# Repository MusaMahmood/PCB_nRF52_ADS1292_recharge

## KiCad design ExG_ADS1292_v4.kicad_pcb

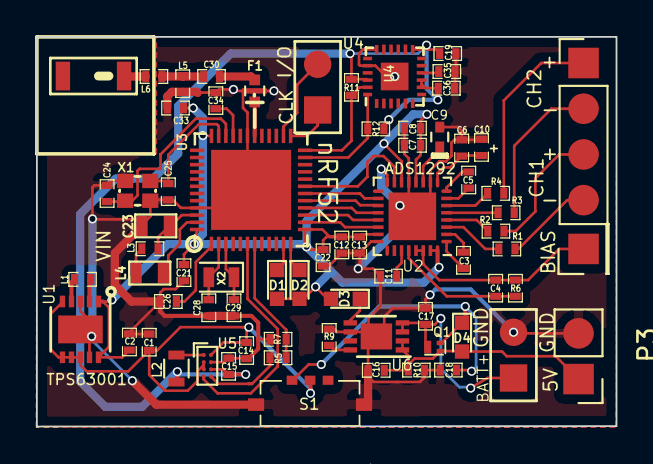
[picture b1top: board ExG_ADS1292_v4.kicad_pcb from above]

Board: 2 copper layers, 32.2 x 21.7 mm, 70 parts (0 on the bottom side), 58 nets.

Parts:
A1: CHIP-ANT; JTI-2450AT18A100-CHIP-ANT
C1, C10, C14, C15: 10uF; SM0402
C2: 22uF; SM0402
C3, C5: 4.7 nF; SM0402
C4: 1.0nF-1.5nF; SM0402
C6, C7, C12: 0.1uF; SM0402
C8, C11, C13: 1uF; SM0402
C9: 1uF; C_0402
C16, C17: 4.7uF; SM0402
C18: 1.0uF; SM0402
C19, C22, C26, C33, C35, C36: 100nF; SM0402
C21: 4.7µF; SM0402
C23: 1.0µF; SM0603
C24, C25, C28, C29: 12pF; SM0402
C30: 1.0pF; SM0402
C34: 100pF; SM0402
D1, D2, D3: LED; LED_0603
D4: D_Schottky; LED_0603
F1: 2450FM07A0029; R_0402
L1: 2.20µH; SM0402
L2: 2.2 uH; R_0603
L3: 15nH; SM0402
L4: 10uH; SM0603
L5: 2.7nH; SM0402
L6: 3.9nH; SM0402
P1, P2: CONN_2; PIN_ARRAY_2X1
P3: CONN_2; Pin_Header_Straight_1x02_Pitch2.54mm
P4: CONN_1; Pin_Header_Straight_1x01_Pitch2.54mm
P5: CONN_01X04; Pin_Header_Straight_1x04_Pitch2.54mm
Q1: DMP21D5UFB4-7B; X2-DFN1006
R1, R2, R3, R4: 30k; SM0402
R5, R7: 1M; SM0402
R6: 1MΩ; SM0402
R9: 2k; SM0402
R10: 100k; SM0402
R11, R12: 10k; SM0402
S1: SSAJ120100
U1: TPS63001; DFN-10-1EP_3x3mm_Pitch0.5mm
U2: ADS1291/2; QFN-32-1EP_4x4mm_Pitch0.4mm
U3: NRF528XX-QFAA; UQFN-48-1EP_6x6mm_Pitch0.4mm
U4: ICM-20948; QFN-24_3x3mm_Pitch0.4mm
U5: TPS62746; Texas_DSBGA-8_0.9x1.9mm_Layout2x4_P0.5mm
U6: MCP73831; DFN-8-1EP_3x2mm_Pitch0.5mm
X1: Crystal_GND24; CRYSTAL-SMD-2.0MMx1.6MM
X2: 32.768 kHz; Crystal_SMD_2012-2pin_2.0x1.2mm

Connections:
1.8V: C15.1, C19.1, C36.1, L2.2, R11.1, R12.1, U4.8, U4.9, U4.13, U4.22, U5.C2
5V_in_charge: C16.1, D4.2, P3.1, Q1.1, R10.1, U6.1, U6.2
/AIN_BAT_DIV_VOLTAGE: R5.2, R7.2, U3.7
/BATT_IN: C17.1, P1.1, Q1.2, U6.3, U6.4
/BIASIN: C4.2, P4.1, R6.2, U2.29, U2.30
/DEC1: C26.1, U3.1
/DEC3: C34.1, U3.33
/DIN: U2.19, U3.17
/DOUT: U2.21, U3.15
/IN1: P5.3, R2.2
/IN1-: P5.4, R1.2
/IN2: P5.1, R4.2
/IN2-: P5.2, R3.2
/LED2: D1.1, U3.11
/LED3: D2.1, U3.12
/LOAD_SW_CTRL: U3.6, U5.D1
/RF: C30.1, F1.4
/SCL: R11.2, U3.24, U4.23
/SDI: R12.2, U3.23, U4.24
/SPI_SCLK: U2.20, U3.16
/SPI_~CS: U2.18, U3.18
/SWDCLK: P2.1, U3.25
/SWDIO: P2.2, U3.26
/~DRDY: U2.22, U3.14
/~PWDN/RESET: U2.15, U3.19
DGND: C1.2, C2.2, C6.1, C7.1, C8.1, C9.2, C10.1, C11.2, C12.2, C13.2, C14.2, C15.2, C16.2, C17.2, C18.1, C19.2, C21.1, C22.2, C23.2, C24.1, C25.1, C26.2, C28.2, C29.2, C33.1, C34.2, C35.2, C36.2, F1.1, F1.3, L5.2, P1.2, P3.2, R7.1, R9.2, R10.2, S1.4, S1.5, U1.3, U1.9, U1.11, U2.10, U2.13, U2.16, U2.24, U2.33, U3.31, U3.45, U3.49, U4.18, U4.20, U4.25, U5.B2, U6.6, U6.9, X1.2, X1.4
DVDD: C2.1, C7.2, C8.2, C12.1, C13.1, C21.2, C22.1, C33.2, D1.2, D2.2, D3.2, U1.1, U1.10, U2.12, U2.14, U2.23, U2.31, U2.32, U3.13, U3.36, U3.48
unnamed: A1.1, L6.2
unnamed: C3.1, U2.1
unnamed: C3.2, U2.2
unnamed: C4.1, R6.1, U2.28
unnamed: C5.1, U2.7
unnamed: C5.2, U2.8
unnamed: C9.1, U2.11
unnamed: C6.2, C10.2, U2.9
unnamed: C11.1, U2.27
unnamed: C23.1, L3.2, U3.46
unnamed: C24.2, U3.34, X1.1
unnamed: C25.2, U3.35, X1.3
unnamed: C28.1, U3.2, X2.2
unnamed: C29.1, U3.3, X2.1
unnamed: C30.2, L5.1, L6.1
unnamed: C35.1, U4.10
unnamed: D3.1, U6.5
unnamed: F1.2, U3.30
unnamed: L1.1, U1.4
unnamed: L1.2, U1.2
unnamed: L2.1, U5.A1
unnamed: L3.1, L4.2
unnamed: L4.1, U3.47
unnamed: R1.1, U2.3
unnamed: R2.1, U2.4
unnamed: R3.1, U2.5
unnamed: R4.1, U2.6
unnamed: R5.1, U5.D2
unnamed: R9.1, U6.8
VCC: C1.1, C14.1, S1.3, U1.5, U1.6, U1.7, U1.8, U5.A2, U5.B1, U5.C1
VccSwitch: C18.2, D4.1, Q1.3, S1.1

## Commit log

2018-06-26 Initial Commit.
2018-06-26 Removed extraneous libs.
2018-06-26 Removed datasheet.
2018-06-26 Minor adjustment + gerber files
2018-06-26 Added updated recharging and load sharing circuit : extra components (Q1, D4, R10, C18).
2018-08-14 Fixed load sharing circuit and PCB (final)
2018-08-14 Removed MPU9250 (EMG only with recharge circuit).
2018-10-16 Updated schematic, pcb and libs.
2019-06-09 Replace pin header holes with pads.
2019-06-09 Added SSAJ switch, fixed annotations.
2019-06-10 Added TPS62746 1.8V regulator, replaced MPU9250 with ICM-20948, added SSAJ switch.
